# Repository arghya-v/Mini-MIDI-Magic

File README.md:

# My Custom MIDI Controller 🎛️

**Author:** Arghya Vyas  
**Created On:** September 29, 2025  
**Description:** A simple custom MIDI controller I designed and built from scratch using KiCad and 3D modeling tools.

## 🧠 Overview
This project documents the creation of my custom MIDI controller, from schematic design in KiCad to PCB routing and 3D chassis modeling in TinkerCad.  
I learned about switch matrices, rotary encoders, I2S DAC modules, and custom footprints.

Project journal in the **ORIGINAL-JOURNAL.md** file!

## Rendered Images

## Features

- Compact 4×5 switch matrix for customizable key input

- Rotary encoders for parameter control (e.g. volume, modulation)

- Slide potentiometer for expressive MIDI control

- LCD screen for real-time feedback and menus

- ADS1015 ADC expansion for additional analog inputs

- I2S DAC output for high-quality audio signals

- Custom PCB design built in KiCad

- 3D-printed chassis with modular top and bottom plates

## 🛠️ Tools Used
- **KiCad 9.0** – schematic & PCB design  
- **TinkerCad** – chassis modeling  
- **Hackclub Slack** – troubleshooting and collaboration  
- **Adafruit** – components & footprint references  
- **Orpheus Pico** – main controller  

## 💡 Reflection
This project was a great learning experience — I learned how to:
- Use KiCad effectively for multi-part designs  
- Understand switch matrices and ADC expansion  
- Create and import custom footprints  
- Transition from schematic to PCB  
- Design a printable chassis in CAD  

Overall, this was my first big hardware project, and I’m really proud of how it turned out!

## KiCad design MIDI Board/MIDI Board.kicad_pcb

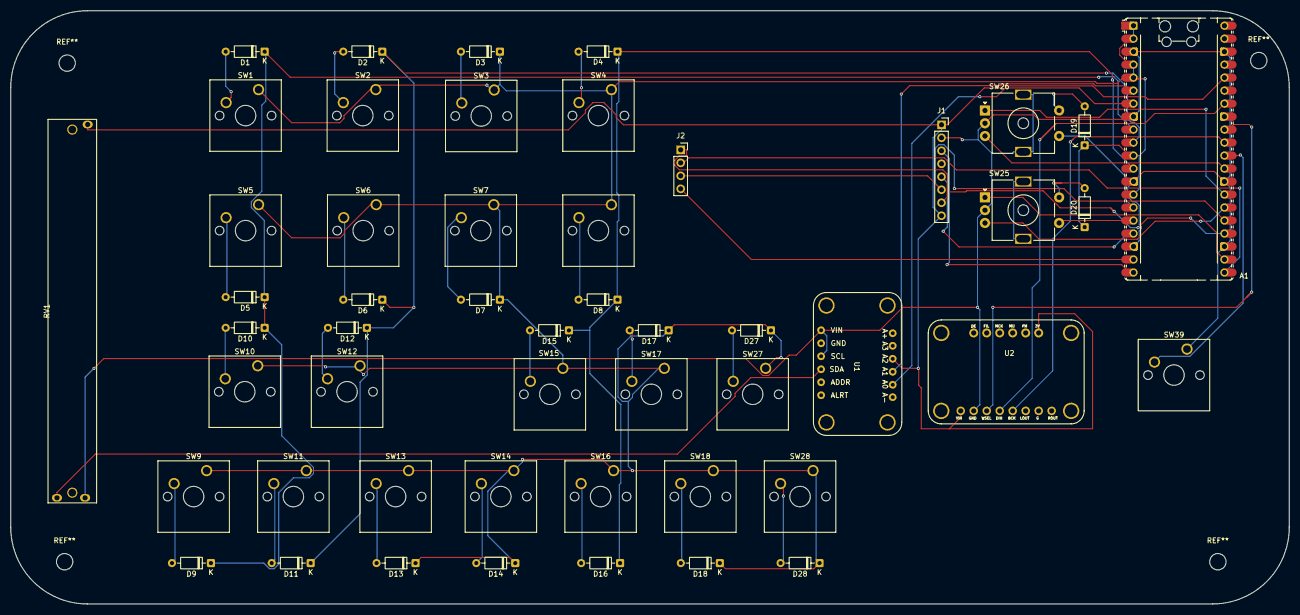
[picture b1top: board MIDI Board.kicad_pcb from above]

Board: 2 copper layers, 250.0 x 116.0 mm, 51 parts (0 on the bottom side), 47 nets.

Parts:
A1: Orpheus Pico; RaspberryPi_Pico_Common_Unspecified
D1, D2, D3, D4, D5, D6, D7, D8, D9, D10, D11, D12, D13, D14, D15, D16, D17, D18, D19, D20, D27, D28: 1N4148; D_DO-35_SOD27_P7.62mm_Horizontal
J1: S37735R; PinSocket_1x08_P2.54mm_Vertical
J2: SD Card; PinSocket_1x04_P2.54mm_Vertical
RV1: Adafruit Slide Pot: 4219; Slide_Pot_75mm_Adafruit4219_fixed
SW1, SW2, SW3, SW4, SW6, SW7, SW8, SW9, SW11, SW12, SW13, SW14, SW15, SW16, SW17, SW18, SW27, SW28, SW39: SW_Push_45deg; SW_Cherry_MX_1.00u_PCB
SW5, SW10: SW5; SW_Cherry_MX_1.00u_PCB
SW25, SW26: RotaryEncoder_Switch_MP; RotaryEncoder_Alps_EC11E-Switch_Vertical_H20mm_MountingHoles
U1: ADS1015; Adafruit_ADS1115
U2: PCM5100; PCM5100 I2S DAC

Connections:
1A: A1.22 (GPIO17), SW25.A
1B: A1.26 (GPIO20), SW25.B
1S1: A1.16 (GPIO12), SW25.S1
1S2: D20.2 (A), SW25.S2
2A: A1.27 (GPIO21), SW26.A
2B: A1.29 (GPIO22), SW26.B
2S1: A1.15 (GPIO11), SW26.S1
2S2: D19.2 (A), SW26.S2
+3V3: A1.36 (3V3), J1.1, J1.8, RV1.3, U1.8 (VDD), U2.1 (VIN), U2.14 (3V)
A0: A1.17 (GPIO13), J1.5
A1: RV1.2, U1.4 (AIN0)
BLCK: A1.31 (GPIO26_ADC0), U2.5 (BCK)
COL0: A1.9 (GPIO6), D1.1 (K), D5.1 (K), D9.1 (K), D10.1 (K)
COL1: A1.10 (GPIO7), D2.1 (K), D6.1 (K), D11.1 (K), D12.1 (K)
COL2: A1.1 (GPIO0), A1.2 (GPIO1), A1.4 (GPIO2), A1.5 (GPIO3), A1.11 (GPIO8), A1.14 (GPIO10), D3.1 (K), D7.1 (K), D13.1 (K), D14.1 (K), D17.1 (K), D18.1 (K), D19.1 (K), D20.1 (K), D27.1 (K), D28.1 (K), SW1.1, SW2.1, SW3.1, SW4.1, SW5.1, SW6.1, SW7.1, SW8.1, SW9.1, SW10.1, SW11.1, SW12.1, SW13.1, SW14.1, SW15.1, SW16.1, SW17.1, SW18.1, SW27.1, SW28.1
COL3: A1.12 (GPIO9), D4.1 (K), D8.1 (K), D15.1 (K), D16.1 (K)
CS_LCD: A1.20 (GPIO15), J1.3
CS_SD: A1.19 (GPIO14), J2.4
DIN: A1.34 (GPIO28_ADC2), U2.4 (DIN)
GND: A1.3 (GND), A1.8 (GND), A1.13 (GND), A1.18 (GND), A1.23 (GND), A1.28 (GND), A1.38 (GND), J1.2, RV1.1, SW25.C, SW26.C, SW26.MP, SW39.1, U1.1 (ADDR), U1.3 (GND), U2.2 (GND)
LRCLK: A1.32 (GPIO27_ADC1), U2.3 (WSEL)
MISO: A1.21 (GPIO16), J2.2
MOSI: A1.25 (GPIO19), J1.6, J2.3
unnamed: A1.6 (GPIO4), U1.9 (SDA)
unnamed: A1.7 (GPIO5), U1.10 (SCL)
unnamed: A1.30 (RUN), SW39.2
unnamed: D1.2 (A), SW1.2
unnamed: D2.2 (A), SW2.2
unnamed: D3.2 (A), SW3.2
unnamed: D4.2 (A), SW4.2
unnamed: D5.2 (A), SW5.2
unnamed: D6.2 (A), SW6.2
unnamed: D7.2 (A), SW7.2
unnamed: D8.2 (A), SW8.2
unnamed: D9.2 (A), SW9.2
unnamed: D10.2 (A), SW10.2
unnamed: D11.2 (A), SW11.2
unnamed: D12.2 (A), SW12.2
unnamed: D13.2 (A), SW13.2
unnamed: D14.2 (A), SW14.2
unnamed: D15.2 (A), SW15.2
unnamed: D16.2 (A), SW16.2
unnamed: D17.2 (A), SW17.2
unnamed: D18.2 (A), SW18.2
unnamed: D27.2 (A), SW27.2
unnamed: D28.2 (A), SW28.2
SCK: A1.24 (GPIO18), J1.7, J2.1

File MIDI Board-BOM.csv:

Reference,Qty,Value,DNP,Exclude from BOM,Exclude from Board,Footprint,Datasheet,Price,Purchase Link
A1,1,Orpheus Pico,,,,Module:RaspberryPi_Pico_Common_Unspecified,https://datasheets.raspberrypi.com/pico/pico-datasheet.pdf,N/A (provided in kit),
"D1,D2,D3,D4,D5,D6,D7,D8,D9,D10,D11,D12,D13,D14,D15,D16,D17,D18,D19,D20,D27,D28",22,1N4148,,,,Diode_THT:D_DO-35_SOD27_P7.62mm_Horizontal,https://assets.nexperia.com/documents/data-sheet/1N4148_1N4448.pdf,N/A (provided in kit),
J1,1,S37735R,,,,Connector_PinSocket_2.54mm:PinSocket_1x08_P2.54mm_Vertical,~,N/A (provided in kit),
J2,1,SD Card,,,,Connector_PinSocket_2.54mm:PinSocket_1x04_P2.54mm_Vertical,~,N/A (provided in kit),
"SW1,SW2,SW3,SW4,SW5,SW6,SW7,SW8,SW9,SW10,SW11,SW12,SW13,SW14,SW15,SW16,SW17,SW18,SW27,SW28,SW39",21,SW_Push_45deg,,,,Button_Switch_Keyboard:SW_Cherry_MX_1.00u_PCB,~,N/A (provided in kit),
"SW25,SW26",2,RotaryEncoder_Switch_MP,,,,Rotary_Encoder:RotaryEncoder_Alps_EC11E-Switch_Vertical_H20mm_MountingHoles,~,N/A (provided in kit),
U2,1,PCM5100,,,,potentiometer:PCM5100 I2S DAC,http://www.ti.com/lit/ds/symlink/pcm5100.pdf,N/A (provided in kit),
,,,,,,,,,
--- Grant-Requested Parts ---,,,,,,,,,
RV1,1,Potentiometer,,,,potentiometer:Slide_Pot_75mm_Adafruit4219_fixed,https://cdn-shop.adafruit.com/product-files/4219/4219_C11375.pdf,$2.95 ,https://www.adafruit.com/product/4219
U1,1,ADS Module (Analog-to-Digital Converter),,,,potentiometer:Adafruit_ADS1015_Module,http://www.ti.com/lit/ds/symlink/ads1015.pdf,$9.95 ,https://www.adafruit.com/product/1083?srsltid=AfmBOop8ixWUQa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
HW1,4,M3  18 mm Screw,,,,Hardware:Screw_M3_18mm,~,$1.06 ,https://us.store.bambulab.com/products/m3-button-head-cap-ma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 
HW2,4,M3 4 mm Screw,,,,Hardware:Screw_M3_4mm,~,$1.06 ,https://us.store.bambulab.com/products/m3-button-head-cap-ma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
HW3,2,M2 5 mm Screw,,,,Hardware:Screw_M2_5mm,~,$1.02 ,https://us.store.bambulab.com/products/m2-button-head-cap-ma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

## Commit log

2025-10-05 Create hi
2025-10-05 Rename Dazzling Lappi-Habbi.stl to pcb-with-case.stl
